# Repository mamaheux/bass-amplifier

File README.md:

# Bass-Amplifier
Bass-Amplifier is a project to create our own bass guitar amplifier. The amplifier features are:
 - Digital sound processing
 - Footswitch
 - Tuner output
 - XLR and jack direct output
 - Effect send and return
 - Contour and presence filters
 - 4-band EQ
 - Compressor effect
 - Overdrive effect
 - Octaver effect
 - Delay effect
 - Reverb effect

## Folder Descriptions
### cases
This folder contains the CAD files to create the cases.

### code
This folder contains the MCU source code for the footswitch, the bass amplifier signal processor and the bass amplifier controller.

### electronics
This folder contains the schematics and PCB layouts of the bass amplifier.

### tools/signal_processing
This folder contains a Python tool to test the audio effects.

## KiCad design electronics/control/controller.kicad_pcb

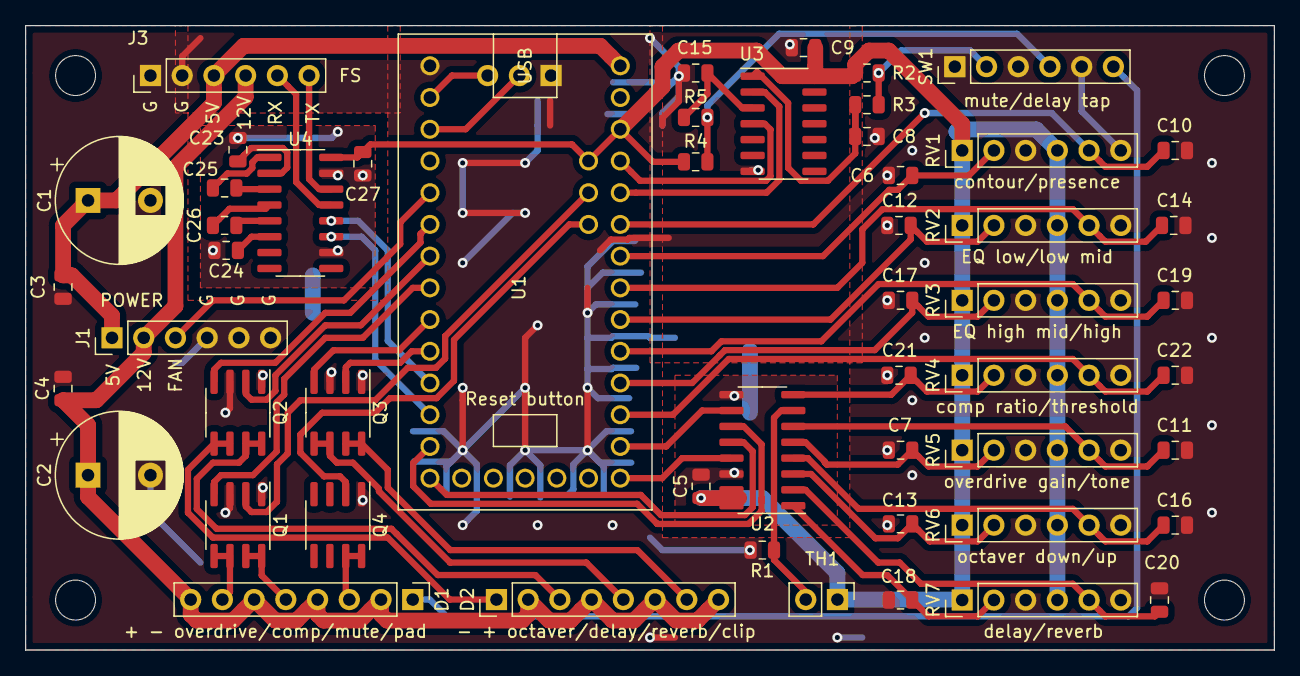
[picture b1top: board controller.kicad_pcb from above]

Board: 2 copper layers, 100.0 x 50.0 mm, 54 parts (1 on the bottom side), 57 nets.

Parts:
C1, C2: 1000µF/25V; CP_Radial_D10.0mm_P5.00mm
C3, C4: 2.2µF/25V/UL low ESR; C_0805_2012Metric
C5, C9: 1µF/10V/UL ESR; C_0805_2012Metric
C6, C7, C10, C11, C12, C13, C14, C16, C17, C18, C19, C20, C21, C22: 1µF/16V; C_0805_2012Metric
C8, C15: 0.1µF/25V; C_0805_2012Metric
C23, C24, C25, C26, C27: 0.1µF; C_0805_2012Metric
D1, D2: LED; PinHeader_1x08_P2.54mm_Vertical
J1: Conn_01x06_Male; PinHeader_1x06_P2.54mm_Vertical
J2: Conn_01x03_Male; PinHeader_1x03_P2.54mm_Vertical
J3: footswitch; PinHeader_1x06_P2.54mm_Vertical
Q1, Q2, Q3, Q4: TD9944; SOIC-8_3.9x4.9mm_P1.27mm
R1, R2, R3, R4, R5: 10k; R_0805_2012Metric
RV1, RV2, RV3, RV4, RV5, RV6, RV7: 10k; PinHeader_1x06_P2.54mm_Vertical
SW1: SW_SPST_X3; PinHeader_1x06_P2.54mm_Vertical
TH1: 10k; PinHeader_1x02_P2.54mm_Vertical
U1: Teensy_LC
U2: MCP3208; SOIC-16_3.9x9.9mm_P1.27mm
U3: 74HC14; SOIC-14_3.9x8.7mm_P1.27mm
U4: MAX3232; SOIC-16_3.9x9.9mm_P1.27mm

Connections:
/MCU/3V3: C5.1, C9.1, C27.1, R2.1, R4.1, RV1.1, RV1.4, RV2.1, RV2.4, RV3.1, RV3.4, RV4.1, RV4.4, RV5.1, RV5.4, RV6.1, RV6.4, RV7.1, RV7.4, TH1.1, U1.3V3_1, U1.AREF, U2.15, U2.16, U3.14, U4.16
/MCU/ADC_CS: U1.14, U2.10
/MCU/ADC_MISO: U1.12, U2.12
/MCU/ADC_MOSI: U1.11, U2.11
/MCU/ADC_SCK: U1.13, U2.13
/MCU/DSP_RX: J2.2, U1.1
/MCU/DSP_TX: J2.3, U1.0
/MCU/FS_RS232_RX: J3.5, U4.13
/MCU/FS_RS232_TX: J3.6, U4.14
/MCU/FS_RX: U1.9, U4.12
/MCU/FS_TX: U1.10, U4.11
/MCU/MCU_LED/clipping_LED: Q3.2, U1.8
/MCU/MCU_LED/delay_LED: Q2.2, U1.5
/MCU/MCU_LED/octaver_LED: Q2.4, U1.4
/MCU/MCU_LED/overdrive_LED: Q1.4, U1.6
/MCU/MCU_LED/reverb_LED: Q3.4, U1.7
/MCU/MCU_control_elements/EQ_high_mid_pot: C17.1, RV3.2, U1.16
/MCU/MCU_control_elements/EQ_high_pot: C19.1, RV3.5, U1.17
/MCU/MCU_control_elements/EQ_low_mid_pot: C14.1, RV2.5, U1.19
/MCU/MCU_control_elements/EQ_low_pot: C12.1, RV2.2, U1.18
/MCU/MCU_control_elements/comp_ratio_pot: C21.1, RV4.2, U2.8
/MCU/MCU_control_elements/comp_threshold_pot: C22.1, RV4.5, U1.15
/MCU/MCU_control_elements/contour_pot: C6.1, RV1.2, U1.20
/MCU/MCU_control_elements/delay_tap_button: U1.23, U3.4
/MCU/MCU_control_elements/delay_vol_pot: C18.1, RV7.2, U2.1
/MCU/MCU_control_elements/mute_sw: U1.22, U3.2
/MCU/MCU_control_elements/octaver_down_pot: C13.1, RV6.2, U2.3
/MCU/MCU_control_elements/octaver_up_pot: C16.1, RV6.5, U2.4
/MCU/MCU_control_elements/overdrive_gain_pot: C7.1, RV5.2, U2.5
/MCU/MCU_control_elements/overdrive_tone_pot: C11.1, RV5.5, U2.6
/MCU/MCU_control_elements/presence_pot: C10.1, RV1.5, U1.21
/MCU/MCU_control_elements/reverb_vol_pot: C20.1, RV7.5, U2.2
/MCU/V_temp: R1.1, TH1.2, U2.7
/MCU/comp_LED: Q1.2, U1.24
/MCU/fan_pwm: J1.3, U1.3
/MCU/mute_LED: Q4.2, U1.25
D+5V: C1.1, C3.1, J1.1, J3.3, U1.VIN
D+12V: C2.1, C4.1, D1.2, D1.4, D1.6, D1.8, D2.2, D2.4, D2.6, D2.8, J1.2, J3.4
GNDD: C1.2, C2.2, C3.2, C4.2, C5.2, C6.2, C7.2, C8.2, C9.2, C10.2, C11.2, C12.2, C13.2, C14.2, C15.2, C16.2, C17.2, C18.2, C19.2, C20.2, C21.2, C22.2, C23.2, C24.2, C27.2, J1.4, J1.5, J1.6, J2.1, J3.1, J3.2, Q1.1, Q1.3, Q2.1, Q2.3, Q3.1, Q3.3, Q4.1, R1.2, RV1.3, RV1.6, RV2.3, RV2.6, RV3.3, RV3.6, RV4.3, RV4.6, RV5.3, RV5.6, RV6.3, RV6.6, RV7.3, RV7.6, SW1.1, SW1.3, SW1.5, U1.GND_1, U2.9, U2.14, U3.7, U4.10, U4.15
unnamed: C8.1, R3.1, U3.1
unnamed: C15.1, R5.1, U3.3
unnamed: C23.1, U4.2
unnamed: C24.1, U4.6
unnamed: C25.1, U4.3
unnamed: C25.2, U4.1
unnamed: C26.1, U4.5
unnamed: C26.2, U4.4
unnamed: D1.1, SW1.6
unnamed: D1.3, Q4.7, Q4.8
unnamed: D1.5, Q1.7, Q1.8
unnamed: D1.7, Q1.5, Q1.6
unnamed: D2.1, Q2.5, Q2.6
unnamed: D2.3, Q2.7, Q2.8
unnamed: D2.5, Q3.5, Q3.6
unnamed: D2.7, Q3.7, Q3.8
unnamed: R2.2, R3.2, SW1.2
unnamed: R4.2, R5.2, SW1.4

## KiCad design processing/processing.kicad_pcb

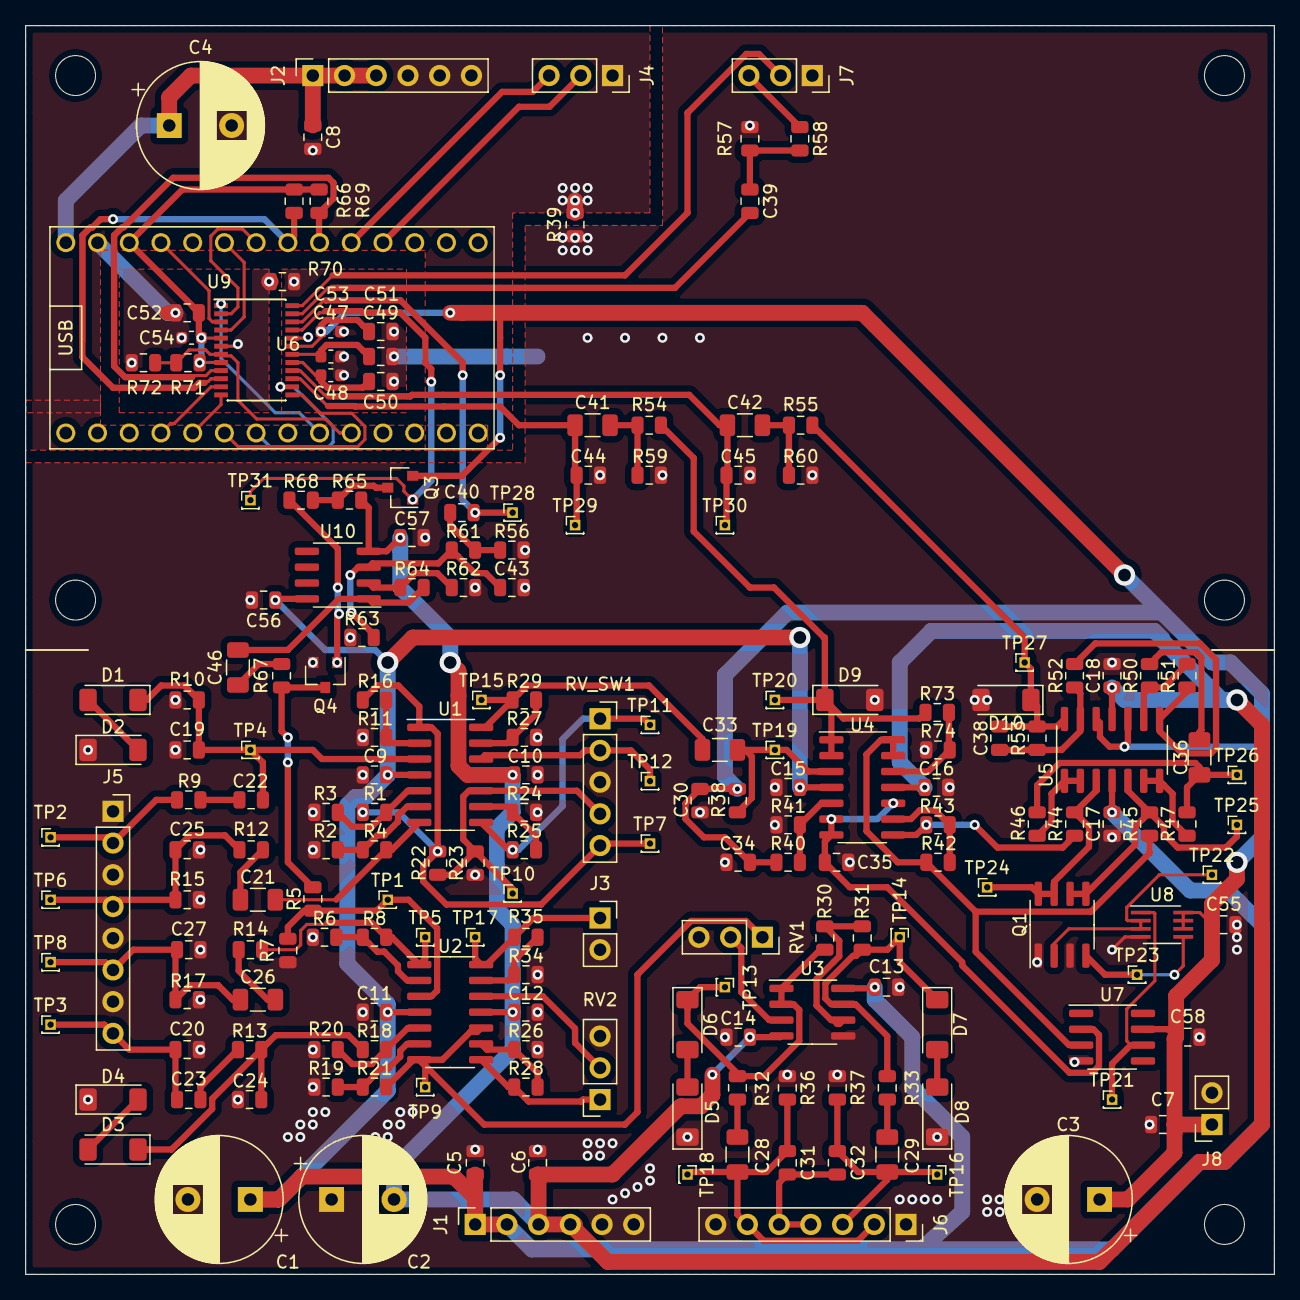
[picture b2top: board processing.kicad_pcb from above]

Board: 2 copper layers, 100.0 x 100.0 mm, 194 parts (0 on the bottom side), 106 nets.

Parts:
C1, C2, C3, C4: 1000µF/25V; CP_Radial_D10.0mm_P5.00mm
C5, C6, C7, C8, C9, C10, C11, C12, C13, C14, C15, C16, C17, C18, C30, C34, C35, C55, C56, C57, C58: 2.2µF/25V/UL ESR; C_0805_2012Metric
C19: 100pF/100V; C_0805_2012Metric
C20, C24: 220pF/100V; C_0805_2012Metric
C21, C26, C28, C29, C33, C36, C41, C42, C46: 10µF/50V; C_1206_3216Metric
C22: 0.1µF/100V; C_0805_2012Metric
C23: 0.22µF/100V; C_0805_2012Metric
C25: 1nF/100V; C_0805_2012Metric
C27, C31, C32: 4.7nF/100V; C_0805_2012Metric
C38: 0.047µF/100V; C_0805_2012Metric
C39, C40: 3.3µF/25V; C_0805_2012Metric
C43: 3600pF/50V; C_0805_2012Metric
C44, C45: 220pF/50V; C_0805_2012Metric
C47, C48, C53, C54: 0.1µF/25V; C_0603_1608Metric
C49: 47µF/10V; C_0805_2012Metric
C50: 10µF/10V; C_0805_2012Metric
C51, C52: 1µF/6.3V; C_0805_2012Metric
D1, D2, D3, D4, D5, D6, D7, D8: 12V; D_1806_4516Metric
D9, D10: 6.2V; D_1806_4516Metric
J1, J2: Conn_01x06_Male; PinSocket_1x06_P2.54mm_Vertical
J3: power_amp; PinSocket_1x02_P2.54mm_Vertical
J4: control board; PinSocket_1x03_P2.54mm_Vertical
J5: AudioJack2_X4; PinSocket_1x08_P2.54mm_Vertical
J6: AudioJack2_XLR_SW; PinSocket_1x07_P2.54mm_Vertical
J7: Conn_01x03_Male; PinSocket_1x03_P2.54mm_Vertical
J8: Conn_01x02_Male; PinSocket_1x02_P2.54mm_Vertical
Q1: TD9944; SOIC-8_3.9x4.9mm_P1.27mm
Q3: MMUN2111LT1; SOT-23
Q4: MMBT2222A; SOT-23
R1, R4, R5, R8, R16, R18, R21, R39, R70: 0; R_0805_2012Metric
R2, R6, R11, R19: inf; R_0805_2012Metric
R3, R12, R15, R30, R31, R38, R40, R41, R42, R43, R53, R56, R57, R63, R65, R73, R74: 10k; R_0805_2012Metric
R7: 47.5k; R_0805_2012Metric
R9: 12.1K; R_0805_2012Metric
R10: 1M; R_0805_2012Metric
R13: 12.1k; R_0805_2012Metric
R14: 221; R_0805_2012Metric
R17: 2.21k; R_0805_2012Metric
R20: 56.2k; R_0805_2012Metric
R22: 23.7k; R_0805_2012Metric
R23, R24, R27, R28, R35, R46, R47, R50: 5.11k; R_0805_2012Metric
R25, R29, R44, R45, R51: 20k; R_0805_2012Metric
R26, R34: 10.2k; R_0805_2012Metric
R32, R33: 1k; R_0805_2012Metric
R36, R37: 100k; R_0805_2012Metric
R52: 4.75k; R_0805_2012Metric
R54, R55, R59, R60, R66, R68, R69: 2k; R_0805_2012Metric
R58, R61: 470; R_0805_2012Metric
R62: 3.09k; R_0805_2012Metric
R64: 15.4k; R_0805_2012Metric
R67: 560; R_0805_2012Metric
R71, R72: inf or 47k; R_0805_2012Metric
RV1, RV2: R_POT; PinSocket_1x03_P2.54mm_Vertical
RV_SW1: 10k; PinSocket_1x05_P2.54mm_Vertical
TP1, TP2, TP3, TP4, TP5, TP6, TP7, TP8, TP9, TP10, TP11, TP12, TP13, TP14, TP15, TP16, TP17, TP18, TP19, TP20, TP21, TP22, TP23, TP24, TP25, TP26, TP27, TP28, TP29, TP30, TP31: TP; PinHeader_1x01_P1.00mm_Vertical
U1, U2, U4, U5: TL074; SOIC-14_3.9x8.7mm_P1.27mm
U3, U10: TL072; SOIC-8_3.9x4.9mm_P1.27mm
U6: Teensy_4.0
U7: MCP6541; SOIC-8_3.9x4.9mm_P1.27mm
U8: SN74AUC1G74; SSOP-8_2.95x2.8mm_P0.65mm
U9: CS4270; TSSOP-24_4.4x7.8mm_P0.65mm

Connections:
/LRCLK: U6.20, U9.2
/MCLK: U6.23, U9.3
/MCU_3.3V: C52.1, C54.1, R66.1, R69.1, R71.2, U6.3V3_1, U9.5, U9.8
/SCL: R66.2, U6.19, U9.10
/SCLK: U6.21, U9.4
/SDA: R69.2, U6.18, U9.9
/SDIN: U6.7, U9.1
/SDOUT: R71.1, R72.2, U6.8, U9.7
/analog/octaver_down/REF+1.65V: C35.1, U4.6, U4.7, U4.10, U7.2
/analog/octaver_down/half_signal_in: R42.2, R45.2, U4.13, U4.14, U7.3
/analog/power_amp_signal: J3.1, R35.1, TP17.1, U2.14
/codec/AD0: U6.2, U9.11
/codec/AD1: U6.3, U9.12
/codec/AD2: U6.4, U9.13
/codec/ADC_input_A: D9.1, R54.2, R73.2, TP20.1, U4.1, U4.2
/codec/ADC_input_B: C38.1, D10.1, R53.1, R55.2, TP27.1, U5.14
/codec/DAC_output: Q4.3, R5.2, R67.1
/codec/INA: C41.1, C44.2, TP29.1, U9.15
/codec/INB: C42.1, C45.2, TP30.1, U9.16
/codec/OUTA: C40.2, TP28.1, U9.22
/codec/OUTB: C39.2, U9.23
/codec/~MUTEA: Q3.1, TP31.1, U9.21
/codec/~MUTEB: J7.2, U9.24
/codec/~RST: U6.5, U9.14
A+3.3V: C3.1, C7.1, C30.1, C34.1, C51.1, C53.1, C55.1, C58.1, J8.1, Q3.2, R38.1, R40.2, U5.10, U5.12, U7.7, U8.6, U8.7, U8.8, U9.19
A+15V: C1.1, C5.1, C9.1, C11.1, C13.1, C15.1, C17.1, C56.1, J1.1, J1.2, U1.4, U2.4, U3.8, U4.4, U5.4, U10.8
A-15V: C2.2, C6.2, C10.1, C12.1, C14.1, C16.1, C18.1, C57.1, J1.3, J1.4, R65.1, U1.11, U2.11, U3.4, U4.11, U5.11, U10.4
D+5V: C4.1, C8.1, J2.1, J2.2, J2.3, U6.VIN
GNDA: C1.2, C2.1, C3.2, C5.2, C6.1, C7.2, C9.2, C10.2, C11.2, C12.2, C13.2, C14.2, C15.2, C16.2, C17.2, C18.2, C19.1, C20.2, C24.2, C25.2, C27.2, C30.2, C34.2, C35.2, C43.1, C44.1, C45.1, C47.2, C48.1, C49.2, C50.1, C51.2, C53.2, C55.2, C56.2, C57.2, C58.2, D2.1, D4.1, D5.1, D8.1, D9.2, D10.2, J1.5, J1.6, J3.2, J5.1, J5.3, J5.5, J5.7, J6.1, J6.7, J7.1, J8.2, Q1.1, Q1.3, Q4.2, R2.2, R3.1, R6.2, R7.1, R10.1, R11.2, R15.2, R17.1, R19.2, R20.1, R23.1, R24.2, R26.2, R27.2, R34.2, R36.1, R37.1, R39.1, R41.1, R56.1, R57.1, R59.1, R60.1, R62.2, R63.1, R70.1, R74.1, RV1.3, RV2.3, RV_SW1.3, U3.5, U7.4, U8.4, U9.20
GNDD: C4.2, C8.2, C52.2, C54.2, J2.4, J2.5, J2.6, J4.1, R39.2, R70.2, R72.1, U6.GND_2, U9.6
unnamed: C19.2, C22.1, D1.1, R10.2, TP4.1, U1.3
unnamed: C20.1, C23.1, J5.8, TP3.1
unnamed: C21.1, R12.2
unnamed: C21.2, R4.1, U1.7
unnamed: C22.2, R9.1
unnamed: C23.2, R13.2
unnamed: C24.1, D3.1, R13.1, R18.2
unnamed: C25.1, J5.4, R12.1, R15.1, TP6.1
unnamed: C26.1, C27.1, J5.6, R17.2, TP8.1
unnamed: C26.2, R14.1
unnamed: C28.1, C31.1, J6.2, J6.6, R36.2, TP18.1
unnamed: C28.2, R32.1
unnamed: C29.1, C32.1, J6.3, R37.2, TP16.1
unnamed: C29.2, R33.1
unnamed: C31.2, C32.2, J6.4, J6.5
unnamed: C33.1, R38.2, TP19.1, U4.3
unnamed: C33.2, R29.1, TP15.1, U1.14
unnamed: C36.1, R50.2
unnamed: C36.2, R46.1, R47.2, TP26.1
unnamed: C38.2, R52.1, R53.2, U5.13
unnamed: C39.1, R57.2, R58.2
unnamed: C40.1, R56.2, R61.2
unnamed: C41.2, R54.1, R59.2
unnamed: C42.2, R55.1, R60.2
unnamed: C43.2, R61.1, R63.2, U10.3
unnamed: C46.1, R67.2
unnamed: C46.2, R64.1, U10.1
unnamed: C47.1, C49.1, U9.18
unnamed: C48.2, C50.2, U9.17
unnamed: D1.2, D2.2
unnamed: D3.2, D4.2
unnamed: D5.2, D6.2
unnamed: D6.1, R30.1, R32.2, TP13.1, U3.1, U3.2
unnamed: D7.1, R31.1, R33.2, TP14.1, U3.7
unnamed: D7.2, D8.2
unnamed: J4.2, U6.16
unnamed: J4.3, U6.17
unnamed: J5.2, R9.2, TP2.1
unnamed: J7.3, R58.1
unnamed: Q1.2, TP22.1, U8.2, U8.3
unnamed: Q1.4, TP23.1, U8.5
unnamed: Q1.5, Q1.6, R45.1, TP25.1, U5.5
unnamed: Q1.7, Q1.8, R44.1, TP24.1, U5.3
unnamed: Q3.3, R65.2, R68.1
unnamed: Q4.1, R68.2
unnamed: R1.1, R3.2, U1.5
unnamed: R1.2, R16.1, R22.2, RV_SW1.5, TP7.1, U1.1
unnamed: R2.1, R4.2, U1.6
unnamed: R5.1, R7.2, TP1.1, U2.3
unnamed: R6.1, R8.2, U2.2
unnamed: R11.1, R16.2, U1.2
unnamed: R8.1, R14.2, TP5.1, U2.1
unnamed: R18.1, R20.2, U2.5
unnamed: R19.1, R21.2, U2.6
unnamed: R21.1, RV1.1, TP9.1, U2.7, U2.10
unnamed: R22.1, R23.2, RV_SW1.4, TP10.1, U1.10
unnamed: R24.1, R25.2, U1.9
unnamed: R25.1, RV_SW1.1, TP11.1, U1.8
unnamed: R26.1, R28.2, U2.9
unnamed: R27.1, R29.2, U1.13
unnamed: R28.1, RV2.1, U2.8
unnamed: R30.2, R31.2, U3.6
unnamed: R34.1, R35.2, U2.13
unnamed: R40.1, R41.2, U4.5
unnamed: R42.1, R43.2, U4.9
unnamed: R43.1, R44.2, U4.8
unnamed: R46.2, U5.1, U5.2
unnamed: R47.1, U5.6, U5.7
unnamed: R50.1, R51.2, U5.9
unnamed: R51.1, R52.2, U5.8
unnamed: R62.1, R64.2, U10.2
unnamed: R73.1, R74.2, U4.12
unnamed: RV1.2, U3.3
unnamed: RV2.2, U2.12
unnamed: RV_SW1.2, TP12.1, U1.12
unnamed: TP21.1, U7.6, U8.1

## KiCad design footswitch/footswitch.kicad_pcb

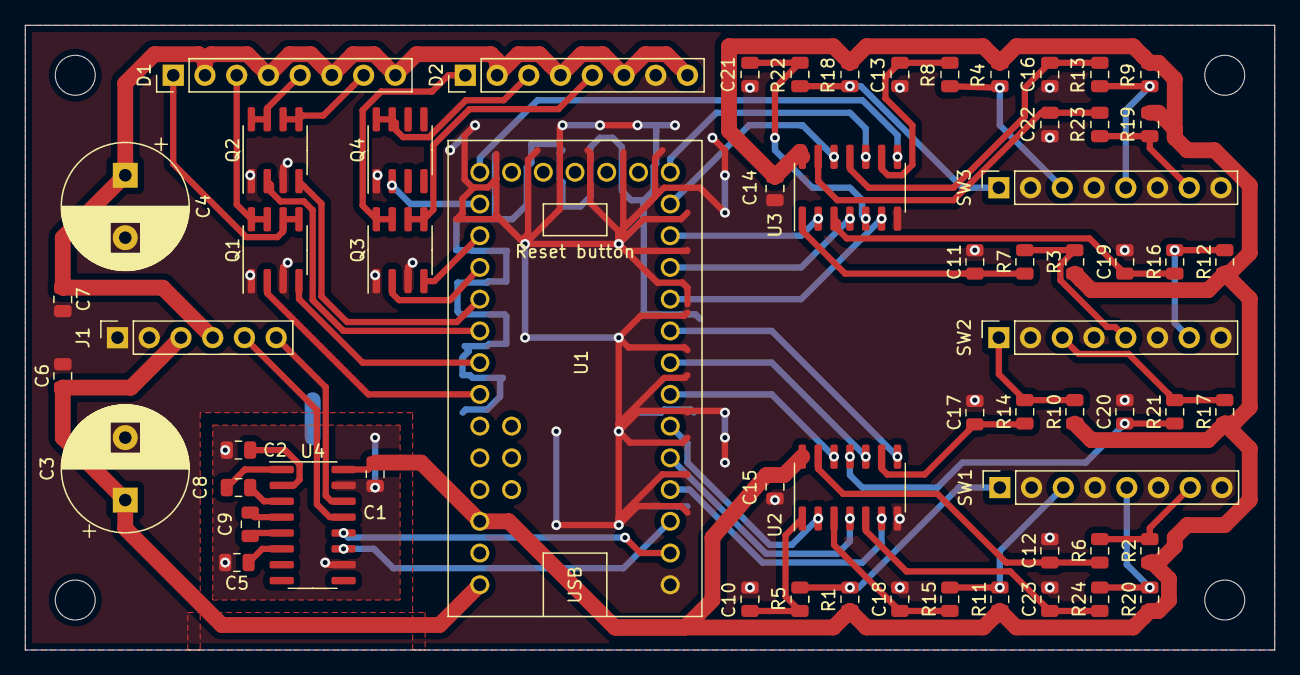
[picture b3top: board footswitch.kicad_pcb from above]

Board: 2 copper layers, 100.0 x 50.0 mm, 61 parts (0 on the bottom side), 64 nets.

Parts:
C1, C2, C5, C8, C9, C10, C11, C12, C13, C16, C17, C18, C19, C20, C21, C22, C23: 0.1µF/25V; C_0805_2012Metric
C3, C4: 1000µF/25V; CP_Radial_D10.0mm_P5.00mm
C6, C7: 2.2µF/25V/UL low ESR; C_0805_2012Metric
C14, C15: 1µF/10V/UL ESR; C_0805_2012Metric
D1, D2: LED; PinHeader_1x08_P2.54mm_Vertical
J1: control; PinSocket_1x06_P2.54mm_Vertical
Q1, Q2, Q3, Q4: TD9944; SOIC-8_3.9x4.9mm_P1.27mm
R1, R2, R3, R4, R5, R6, R7, R8, R9, R10, R11, R12, R13, R14, R15, R16, R17, R18, R19, R20, R21, R22, R23, R24: 10k; R_0805_2012Metric
SW1, SW2, SW3: SPST; PinSocket_1x08_P2.54mm_Vertical
U1: Teensy_LC
U2, U3: 74HC14; SOIC-14_3.9x8.7mm_P1.27mm
U4: MAX3232; SOIC-16_3.9x9.9mm_P1.27mm

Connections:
/3V3: C1.2, C14.1, C15.1, R1.1, R2.1, R3.1, R4.1, R9.1, R10.1, R11.1, R12.1, R17.1, R18.1, R19.1, R20.1, U1.3V3_1, U2.14, U3.14, U4.16
/MCU_LED/clipping_LED: Q1.4, U1.19
/MCU_LED/comp_LED: Q2.2, U1.18
/MCU_LED/delay_LED: Q4.2, U1.14
/MCU_LED/mute_LED: Q1.2, U1.20
/MCU_LED/octaver_LED: Q3.2, U1.16
/MCU_LED/overdrive_LED: Q2.4, U1.17
/MCU_LED/reverb_LED: Q3.4, U1.15
/MCU_switchs/comp_sw: U1.3, U2.4
/MCU_switchs/delay_sw: U1.7, U2.8
/MCU_switchs/delay_tap_button: U1.6, U2.10
/MCU_switchs/mute_sw: U1.4, U2.2
/MCU_switchs/octaver_sw: U1.5, U2.12
/MCU_switchs/opt_1_sw: U1.9, U3.4
/MCU_switchs/opt_2_sw: U1.8, U3.6
/MCU_switchs/opt_3_sw: U1.13, U3.8
/MCU_switchs/opt_4_sw: U1.12, U3.10
/MCU_switchs/opt_5_sw: U1.11, U3.12
/MCU_switchs/overdrive_sw: U1.2, U2.6
/MCU_switchs/reverb_sw: U1.10, U3.2
/control_RX: U1.0, U4.12
/control_TX: U1.1, U4.11
D+5V: C3.1, C6.1, J1.3, U1.VIN
D+12V: C4.1, C7.1, D1.2, D1.4, D1.6, D1.8, D2.2, D2.4, D2.6, D2.8, J1.4
GNDD: C1.1, C2.2, C3.2, C4.2, C5.2, C6.2, C7.2, C10.2, C11.2, C12.2, C13.2, C14.2, C15.2, C16.2, C17.2, C18.2, C19.2, C20.2, C21.2, C22.2, C23.2, D2.7, J1.1, J1.2, Q1.1, Q1.3, Q2.1, Q2.3, Q3.1, Q3.3, Q4.1, SW1.2, SW1.4, SW1.6, SW1.8, SW2.2, SW2.4, SW2.6, SW2.8, SW3.2, SW3.4, SW3.6, SW3.8, U1.GND_1, U2.7, U3.7, U4.10, U4.15
unnamed: C2.1, U4.2
unnamed: C5.1, U4.6
unnamed: C8.1, U4.1
unnamed: C8.2, U4.3
unnamed: C9.1, U4.4
unnamed: C9.2, U4.5
unnamed: C10.1, R5.1, U2.1
unnamed: C11.1, R7.1, U3.1
unnamed: C12.1, R6.1, U2.13
unnamed: C13.1, R8.1, U3.9
unnamed: C16.1, R13.1, U3.11
unnamed: C17.1, R14.1, U2.9
unnamed: C18.1, R15.1, U2.3
unnamed: C19.1, R16.1, U3.3
unnamed: C20.1, R21.1, U2.11
unnamed: C21.1, R22.1, U3.5
unnamed: C22.1, R23.1, U3.13
unnamed: C23.1, R24.1, U2.5
unnamed: D1.1, Q1.5, Q1.6
unnamed: D1.3, Q1.7, Q1.8
unnamed: D1.5, Q2.7, Q2.8
unnamed: D1.7, Q2.5, Q2.6
unnamed: D2.1, Q3.7, Q3.8
unnamed: D2.3, Q4.7, Q4.8
unnamed: D2.5, Q3.5, Q3.6
unnamed: J1.5, U4.13
unnamed: J1.6, U4.14
unnamed: R1.2, R5.2, SW1.1
unnamed: R2.2, R6.2, SW1.7
unnamed: R3.2, R7.2, SW2.5
unnamed: R4.2, R8.2, SW3.3
unnamed: R10.2, R14.2, SW2.1
unnamed: R11.2, R15.2, SW1.3
unnamed: R12.2, R16.2, SW2.7
unnamed: R9.2, R13.2, SW3.5
unnamed: R17.2, R21.2, SW2.3
unnamed: R18.2, R22.2, SW3.1
unnamed: R19.2, R23.2, SW3.7
unnamed: R20.2, R24.2, SW1.5

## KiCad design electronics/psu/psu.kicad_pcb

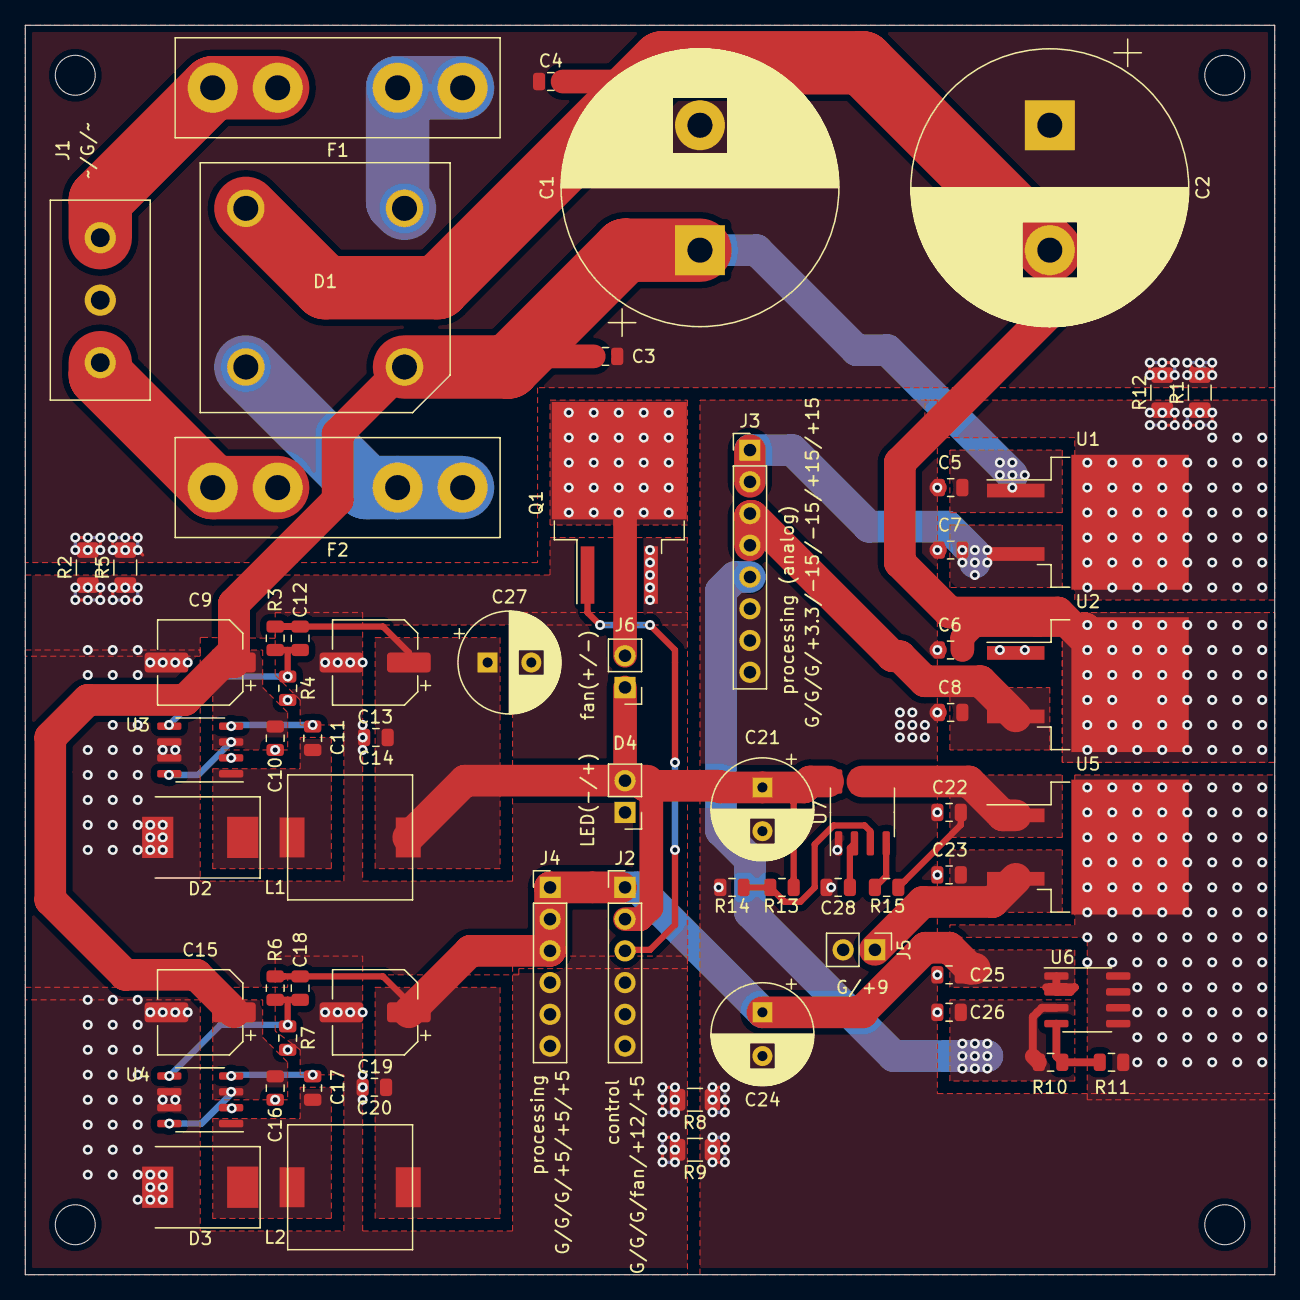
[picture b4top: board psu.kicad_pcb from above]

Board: 2 copper layers, 100.0 x 100.0 mm, 65 parts (0 on the bottom side), 28 nets.

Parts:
C1, C2: 10000µF/35V; CP_Radial_D22.0mm_P10.00mm_SnapIn
C3, C4, C5, C6, C10, C16, C25: 1µF/35V; C_0805_2012Metric
C7, C8, C14, C20, C22, C23: 2.2µF/25V/UL ESR; C_0805_2012Metric
C9, C15: 33µF/35V/260mOhm; CP_Elec_6.3x7.7
C11, C17: 0.33µF; C_0805_2012Metric
C12, C18: 0.1µF; C_0805_2012Metric
C13, C19: 330µF/6.3V/160mOhm; CP_Elec_6.3x7.7
C21, C24, C27: 470µF/16V; CP_Radial_D8.0mm_P3.50mm
C26: 47µF/6.3V; C_0805_2012Metric
C28: C; C_0805_2012Metric
D1: BR81
D2, D3: SS34/40V/4A; D_SMC
D4: LED; PinHeader_1x02_P2.54mm_Vertical
F1, F2: 1.5A; M205_FUSE
J1: Conn_01x03_Female; transformer_connector
J2: control board; PinHeader_1x06_P2.54mm_Vertical
J3: processing; PinHeader_1x08_P2.54mm_Vertical
J4: processing; PinHeader_1x06_P2.54mm_Vertical
J5: pedals; PinHeader_1x02_P2.54mm_Vertical
J6: FAN; PinHeader_1x02_P2.54mm_Vertical
L1, L2: 68µH/Sumida CDRH104R-680MC; CDRH104RNP-680NC
Q1: PHB21N06LT; TO-263-2
R1, R2, R5, R8, R9, R12: 0; R_1206_3216Metric
R3, R6: 3.01k; R_0805_2012Metric
R4: 348; R_0805_2012Metric
R7: 976; R_0805_2012Metric
R10: 16.5k; R_0805_2012Metric
R11: 10k; R_0805_2012Metric
R13, R14: inf; R_0805_2012Metric
R15: 309; R_0805_2012Metric
U1: MC7815; TO-263-2
U2: MC7915; TO-263-2
U3, U4: MIC4684; SOIC-8_3.9x4.9mm_P1.27mm
U5: MC7809; TO-263-2
U6: MIC37152; SOIC-8_3.9x4.9mm_P1.27mm
U7: NIS5112; SOIC-8_3.9x4.9mm_P1.27mm

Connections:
/+20V: C1.1, C3.1, C5.1, C9.1, C10.1, C15.1, C16.1, D1.1, U1.1, U3.3, U3.8, U4.3, U4.8
/-20V: C2.2, C4.2, C6.2, D1.2, U2.2
/A+3.3V: C26.1, J3.5, R10.1, U6.3
/A+9V: C23.1, J5.1, U5.3
/A+15V: C7.1, J3.1, J3.2, U1.3
/A-15V: C8.2, J3.3, J3.4, U2.3
/D+5V: C18.1, C19.1, C20.1, C24.1, C25.1, J2.1, J4.1, J4.2, J4.3, L2.2, R6.1, U6.1, U6.2
/D+12V: C12.1, C13.1, C14.1, C21.1, C27.1, D4.2, J2.2, J6.1, L1.2, R3.1, R13.2, U7.8
/fan/fan_pwm: J2.3, Q1.1
GND: C1.2, C2.1, C3.2, C4.1, J1.2, R1.2, R2.2, R5.2, R12.2
GNDA: C5.2, C6.1, C7.2, C8.1, C21.2, C22.2, C23.2, C24.2, C25.2, C26.2, C28.2, J3.6, J3.7, J3.8, J5.2, R1.1, R8.1, R9.1, R11.2, R12.1, R14.2, U1.2, U2.1, U5.2, U6.5, U6.6, U6.7, U6.8, U7.1
GNDD: C9.2, C10.2, C13.2, C14.2, C15.2, C16.2, C19.2, C20.2, C27.2, D2.2, D3.2, D4.1, J2.4, J2.5, J2.6, J4.4, J4.5, J4.6, Q1.3, R2.1, R4.2, R5.1, R7.2, R8.2, R9.2, U3.2, U3.6, U3.7, U4.2, U4.6, U4.7
unnamed: C11.1, U3.4
unnamed: C11.2, D2.1, L1.1, U3.1
unnamed: C12.2, R3.2, R4.1, U3.5
unnamed: C17.1, U4.4
unnamed: C17.2, D3.1, L2.1, U4.1
unnamed: C18.2, R6.2, R7.1, U4.5
unnamed: C22.1, R15.2, U5.1, U7.5, U7.6, U7.7
unnamed: C28.1, U7.2
unnamed: D1.3, F2.1
unnamed: D1.4, F1.1
unnamed: F1.2, J1.3
unnamed: F2.2, J1.1
unnamed: J6.2, Q1.2
unnamed: R10.2, R11.1, U6.4
unnamed: R13.1, R14.1, U7.3
unnamed: R15.1, U7.4

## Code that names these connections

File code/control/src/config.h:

#ifndef CONFIG_H
#define CONFIG_H

#include <Arduino.h>
#include <SPI.h>

// Effects
constexpr float SAMPLING_FREQUENCY = 48000;
constexpr uint32_t MAX_DELAY = 96000;

// IO
#define DEBUG_SERIAL Serial
#define FOOTSWITCH_SERIAL Serial2
#define DSP_SERIAL Serial1

constexpr uint8_t ADC_RESOLUTION = 12;
constexpr uint16_t ADC_MAX_VALUE = 4095;

#define EXTERNAL_ADC_SPI SPI
constexpr uint32_t EXTERNAL_ADC_SPI_CLK = 1600000;
constexpr uint8_t EXTERNAL_ADC_CS_PIN = 14;

enum class AdcSource
{
    INTERNAL_ADC,
    EXTERNAL_ADC
};

struct AdcChannel
{
    AdcSource source;
    uint8_t channel;
};

constexpr uint16_t POT_DEAD_ZONE = 64;

constexpr AdcChannel CONTOUR_GAIN_POT = {AdcSource::INTERNAL_ADC, 20};
constexpr AdcChannel PRESENCE_GAIN_POT = {AdcSource::INTERNAL_ADC, 21};
constexpr AdcChannel EQ_LOW_GAIN_POT = {AdcSource::INTERNAL_ADC, 18};
constexpr AdcChannel EQ_LOW_MID_GAIN_POT = {AdcSource::INTERNAL_ADC, 19};
constexpr AdcChannel EQ_HIGH_MID_GAIN_POT = {AdcSource::INTERNAL_ADC, 16};
constexpr AdcChannel EQ_HIGH_GAIN_POT = {AdcSource::INTERNAL_ADC, 17};
constexpr AdcChannel COMPRESSOR_THRESHOLD_POT = {AdcSource::INTERNAL_ADC, 15};
constexpr AdcChannel COMPRESSOR_RATIO_POT = {AdcSource::EXTERNAL_ADC, 7};
constexpr AdcChannel OCTAVER_DOWM_VOLUME_POT = {AdcSource::EXTERNAL_ADC, 2};
constexpr AdcChannel OCTAVER_UP_VOLUME_POT = {AdcSource::EXTERNAL_ADC, 3};
constexpr AdcChannel DELAY_VOLUME_POT = {AdcSource::EXTERNAL_ADC, 0};
constexpr AdcChannel REVERB_VOLUME_POT = {AdcSource::EXTERNAL_ADC, 1};
constexpr AdcChannel OVERDRIVE_GAIN_POT = {AdcSource::EXTERNAL_ADC, 4};
constexpr AdcChannel OVERDRIVE_TONE_POT = {AdcSource::EXTERNAL_ADC, 5};

constexpr uint8_t DELAY_TAP_PIN = 23;
constexpr uint8_t MUTE_PIN = 22;


constexpr uint8_t COMPRESSOR_LED_PIN = 24;
constexpr uint8_t OCTAVER_LED_PIN = 4;
constexpr uint8_t DELAY_LED_PIN = 5;
constexpr uint8_t REVERB_LED_PIN = 7;
constexpr uint8_t OVERDRIVE_LED_PIN = 6;
constexpr uint8_t MUTE_LED_PIN = 25;
constexpr uint8_t CLIPPING_LED_PIN = 8;

// Other
constexpr uint32_t CLIPPING_LED_ON_DURATION_MS = 500;

#endif

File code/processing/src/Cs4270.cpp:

#include "Cs4270.h"

#include "InterruptLock.h"

static constexpr uint32_t I2S_TCSR_FRF = 0x00010000;
static constexpr uint32_t I2S_RCSR_FRF = 0x00010000;

static constexpr uint32_t TX_FIFO_WATERMARK = 28;
static constexpr uint32_t RX_FIFO_WATERMARK = 1;


static Cs4270Buffer<BLOCK_SIZE>* leftInputBuffer;
static Cs4270Buffer<BLOCK_SIZE>* rightInputBuffer;
static Cs4270Buffer<BLOCK_SIZE>* leftOutputBuffer;
static Cs4270Buffer<BLOCK_SIZE>* rightOutputBuffer;

static void cs4270Interrupt()
{
    constexpr int32_t SAMPLE_MASK = 0xFFFFFF00;

    if (I2S1_TCSR & I2S_TCSR_FRF)
    {
        // Write samples
        int32_t leftSample = 0;
        int32_t rightSample = 0;

        leftOutputBuffer->read(leftSample);
        rightOutputBuffer->read(rightSample);

        I2S1_TDR0 = leftSample & SAMPLE_MASK;
        I2S1_TDR0 = rightSample & SAMPLE_MASK;
    }

    if (I2S1_RCSR & I2S_RCSR_FRF)
    {
        // Read samples
        int32_t leftSample = I2S1_RDR0;
        int32_t rightSample = I2S1_RDR0;

        leftInputBuffer->write(leftSample & SAMPLE_MASK);
        rightInputBuffer->write(rightSample & SAMPLE_MASK);
    }
}


Cs4270::Cs4270()
{
    static_assert(CS4270_SDIN_PIN == 7, "Invalid SDIN pin");
    static_assert(CS4270_SDOUT_PIN == 8, "Invalid SDOUT pin");
    static_assert(CS4270_LRCLK_PIN == 20, "Invalid LRCLK pin");
    static_assert(CS4270_SCLK_PIN == 21, "Invalid SCLK pin");
    static_assert(CS4270_MCLK_PIN == 23, "Invalid MCLK pin");
}

void Cs4270::begin()
{
    CCM_CCGR5 |= CCM_CCGR5_SAI1(CCM_CCGR_ON);

    setupCs4270();
    setupI2s();
}

bool Cs4270::read(float* leftBlock, float* rightBlock)
{
    InterruptLock lock(IRQ_SAI1);
    if (m_leftInputBuffer.readAvailable() < BLOCK_SIZE || m_rightInputBuffer.readAvailable() < BLOCK_SIZE)
    {
        return false;
    }


    for (uint32_t i = 0; i < BLOCK_SIZE; i++)
    {
        int32_t leftSample;
        int32_t rightSample;

        m_leftInputBuffer.read(leftSample);
        m_rightInputBuffer.read(rightSample);

        leftBlock[i] = int32ToFloat(leftSample);
        rightBlock[i] = int32ToFloat(rightSample);
    }

    return true;
}

bool Cs4270::write(float* leftBlock, float* rightBlock)
{
    InterruptLock lock(IRQ_SAI1);
    if (m_leftOutputBuffer.writeAvailable() < BLOCK_SIZE || m_rightOutputBuffer.writeAvailable() < BLOCK_SIZE)
    {
        return false;
    }

    for (uint32_t i = 0; i < BLOCK_SIZE; i++)
    {
        m_leftOutputBuffer.write(floatToInt32(leftBlock[i]));
        m_rightOutputBuffer.write(floatToInt32(rightBlock[i]));
    }

    return true;
}

void Cs4270::setupCs4270()
{
    setupCs4270Pins();

    CS4270_I2C.begin();
    setupCs4270Parameters();
}

void Cs4270::setupCs4270Pins()
{
    pinMode(CS4270_AD0_PIN, OUTPUT);
    digitalWrite(CS4270_AD0_PIN, LOW);

    pinMode(CS4270_AD1_PIN, OUTPUT);
    digitalWrite(CS4270_AD1_PIN, LOW);

    pinMode(CS4270_AD2_PIN, OUTPUT);
    digitalWrite(CS4270_AD2_PIN, HIGH);

    pinMode(CS4270_RESET_PIN, OUTPUT);
    digitalWrite(CS4270_RESET_PIN, HIGH);
}

void Cs4270::setupCs4270Parameters()
{
    // Default values are good.
}

void Cs4270::setupI2s()
{
    // if TX or RX are enabled
    if ((I2S1_TCSR & I2S_TCSR_TE) || (I2S1_RCSR & I2S_RCSR_RE)) return;

    setupI2sClocks();

    //Setup I2S (TX is sync and RX is async because TX and RX must use RX_BCLK and RX_SYNC)
    setupI2sTx();
    setupI2sRx();

    setupInterrupt();

    enableI2s();
}

void Cs4270::setupI2sClocks()
{
    int n1;
    int n2;
    setupPLL4(n1, n2);
    // Setup SAI1_CLK
    CCM_CSCMR1 = (CCM_CSCMR1 & ~(CCM_CSCMR1_SAI1_CLK_SEL_MASK)) | CCM_CSCMR1_SAI1_CLK_SEL(2); // Set PLL4 clock source
    CCM_CS1CDR = (CCM_CS1CDR & ~(CCM_CS1CDR_SAI1_CLK_PRED_MASK | CCM_CS1CDR_SAI1_CLK_PODF_MASK))
           | CCM_CS1CDR_SAI1_CLK_PRED(n1 - 1) // Set clock pred to n1 (1 <= n1 <= 8)
           | CCM_CS1CDR_SAI1_CLK_PODF(n2 - 1); // Set clock prodf to n1 (1 <= n1 <= 2^6)

    // Setup MCLK1
    IOMUXC_GPR_GPR1 = (IOMUXC_GPR_GPR1 & ~(IOMUXC_GPR_GPR1_SAI1_MCLK1_SEL_MASK))
        | IOMUXC_GPR_GPR1_SAI1_MCLK_DIR // Set MCLK as an output
        | IOMUXC_GPR_GPR1_SAI1_MCLK1_SEL(0); // Set MCLK source to ccm.ssi1_clk_root

    // Setup clock pins
    CORE_PIN23_CONFIG = 3;  // Set pin23 as MCLK
    CORE_PIN21_CONFIG = 3;  // Set pin21 as RX_BCLK
    CORE_PIN20_CONFIG = 3;  // Set pin20 as RX_SYNC
}

void Cs4270::setupPLL4(int& n1, int& n2)
{
    int fs = SAMPLING_FREQUENCY;
    n1 = 4;
    n2 = 1 + (24000000 * 27) / (fs * 256 * n1);

    double C = ((double)fs * 256 * n1 * n2) / 24000000;
    int c0 = C;
    uint32_t c2 = 10000;
    int32_t c1 = C * c2 - (c0 * c2);

    // From :https://github.com/PaulStoffregen/Audio/blob/master/utility/imxrt_hw.cpp
    if (CCM_ANALOG_PLL_AUDIO & CCM_ANALOG_PLL_AUDIO_ENABLE) return;

    CCM_ANALOG_PLL_AUDIO = CCM_ANALOG_PLL_AUDIO_BYPASS | CCM_ANALOG_PLL_AUDIO_ENABLE
                 | CCM_ANALOG_PLL_AUDIO_POST_DIV_SELECT(2) // 2: 1/4; 1: 1/2; 0: 1/1
                 | CCM_ANALOG_PLL_AUDIO_DIV_SELECT(c0);

    CCM_ANALOG_PLL_AUDIO_NUM   = c1 & CCM_ANALOG_PLL_AUDIO_NUM_MASK;
    CCM_ANALOG_PLL_AUDIO_DENOM = c2 & CCM_ANALOG_PLL_AUDIO_DENOM_MASK;

    CCM_ANALOG_PLL_AUDIO &= ~CCM_ANALOG_PLL_AUDIO_POWERDOWN;//Switch on PLL
    while (!(CCM_ANALOG_PLL_AUDIO & CCM_ANALOG_PLL_AUDIO_LOCK)) {}; //Wait for pll-lock

    const int div_post_pll = 1; // other values: 2,4
    CCM_ANALOG_MISC2 &= ~(CCM_ANALOG_MISC2_DIV_MSB | CCM_ANALOG_MISC2_DIV_LSB);
    if(div_post_pll>1) CCM_ANALOG_MISC2 |= CCM_ANALOG_MISC2_DIV_LSB;
    if(div_post_pll>3) CCM_ANALOG_MISC2 |= CCM_ANALOG_MISC2_DIV_MSB;

    CCM_ANALOG_PLL_AUDIO &= ~CCM_ANALOG_PLL_AUDIO_BYPASS;//Disable Bypass
}

void Cs4270::setupI2sTx()
{
    I2S1_TMR = 0; // Set the transmit mask to 0
    I2S1_TCR1 = I2S_TCR1_RFW(TX_FIFO_WATERMARK); // Set the FIFO watermark
    I2S1_TCR2 = I2S_TCR2_SYNC(1) // Set TX mode to sync
        | I2S_TCR2_BCP // Set BCLK active low
        | I2S_TCR2_BCD // Set BCLK as an output
        | I2S_TCR2_DIV(1) // Set bit clock divide to 4
        | I2S_TCR2_MSEL(1); // Set MCLK to MCLK1
    I2S1_TCR3 = I2S_TCR3_TCE; // Enable the first transmit data channel
    I2S1_TCR4 = I2S_TCR4_FRSZ((2 - 1)) // Set 2 words per frame
        | I2S_TCR4_SYWD((32 - 1)) // Set SYNC width to 32;
        | I2S_TCR4_MF // Set MSB first
        | I2S_TCR4_FSD // Set SYNC as an output
        | I2S_TCR4_FSP; // Set SYNC active low
    I2S1_TCR5 = I2S_TCR5_WNW((32 - 1)) // Set the word width to 32
        | I2S_RCR5_W0W((32 - 1)) // Set the word 0 width to 32
        | I2S_RCR5_FBT((32 - 1)); // Set the first bit shifted to 32
}

void Cs4270::setupI2sRx()
{
    I2S1_RMR = 0; // Set the receive mask to 0
    I2S1_RCR1 = I2S_RCR1_RFW(RX_FIFO_WATERMARK); // Set the FIFO watermark
    I2S1_RCR2 = I2S_RCR2_SYNC(0) // Set RX mode to async
        | I2S_RCR2_BCP // Set BCLK active low
        | I2S_RCR2_BCD // Set BCLK as an output
        | I2S_RCR2_DIV(1) // Set bit clock divide to 4
        | I2S_RCR2_MSEL(1); // Set MCLK to MCLK1
    I2S1_RCR3 = I2S_RCR3_RCE; // Enable the first transmit data channel
    I2S1_RCR4 = I2S_RCR4_FRSZ((2 - 1)) // Set 2 words per frame
        | I2S_RCR4_SYWD((32 - 1)) // Set SYNC width to 32;
        | I2S_RCR4_MF // Set MSB first
        | I2S_RCR4_FSD // Set SYNC as an output
        | I2S_RCR4_FSP; // Set SYNC active low
    I2S1_RCR5 = I2S_RCR5_WNW((32-1)) // Set the word width to 32
        | I2S_RCR5_W0W((32-1)) // Set the word 0 width to 32
        | I2S_RCR5_FBT((32-1)); // Set the first bit shifted to 32
}

void Cs4270::setupInterrupt()
{
    leftInputBuffer = &m_leftInputBuffer;
    rightInputBuffer = &m_rightInputBuffer;
    leftOutputBuffer = &m_leftOutputBuffer;
    rightOutputBuffer = &m_rightOutputBuffer;
    attachInterruptVector(IRQ_SAI1, cs4270Interrupt);
}

void Cs4270::enableI2s()
{
    // Offset the output by 1 sample to prevent transmit FIFO errors
    I2S1_TDR0 = 0;
    I2S1_TDR0 = 0;

    // Setup TX/RX pins
    CORE_PIN7_CONFIG  = 3;  // Set pin7 as TX
    CORE_PIN8_CONFIG  = 3;  // Set pin8 as RX
    IOMUXC_SAI1_RX_DATA0_SELECT_INPUT = 2;

    I2S1_TCSR = I2S_TCSR_TE // Enable the transmitter
        | I2S_TCSR_BCE // Enable BCLK
        | I2S_TCSR_FRIE; // Enable transmitter FIFO interrupt

    I2S1_RCSR = I2S_RCSR_RE // Enable the receiver
        | I2S_RCSR_BCE // Enable BCLK
        | I2S_RCSR_FRIE // Enable receiver FIFO interrupt
        | I2S_RCSR_FR; // Reset FIFO
}

float Cs4270::int32ToFloat(int32_t v)
{
    return -static_cast<float>(v) / static_cast<float>(INT32_MIN);
}

int32_t Cs4270::floatToInt32(float v)
{
    if (v < -CLIPPING_VALUE)
    {
        v = INT32_MIN * CLIPPING_VALUE;
    }
    if (v > CLIPPING_VALUE)
    {
        v = INT32_MAX * CLIPPING_VALUE;
    }

    return static_cast<int32_t>(-v * static_cast<float>(INT32_MIN));
}

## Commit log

2020-03-02 Ajout de la shématique pour la partie analogique.
2020-03-02 Ajout de la schématique pour le MCU
2020-03-02 Modification des MOSFET des LED.
2020-03-02 Création d'un projet pour le MCU et finalisation du MCU.
2020-03-02 Ajout du octaver down, ajout du filtre d'anti-aliasing, ajout de l'offset DC et ajout du clipping.
2020-03-02 Enlèvemnt des fichiers de simulation inutile. Ajustement de la fréquence de coupure du filtre d'anti-aliasing.
2020-03-03 Ajout du pcb pour control
2020-03-03 Correction de pad non connecté
2020-03-03 Correciton du PCB (espacements entre les connecteurs et polygon pour pour l'ADC.)
2020-03-03 Ajout des du circuit du psu
2020-03-09 Ajout du connecteur pour la footswitch.
2020-03-09 Ajout du projet et de la schématique de footswitch
2020-03-09 Suppresion des fichier *-bak
2020-03-10 Commencement du PCB pour footswitch
2020-03-10 Ajout du gnd pour le RX/TX du DSP
2020-03-10 Finalisation du PCB de la footswitch. Correction de la position des mounting holes.
2020-03-10 Ajout de documentation dans les schématiques
2020-03-12 Ajout du PCB du PSU
2020-03-12 Ajout du codec et du dsp
2020-03-16 Ajout des pièces du PCB processing au BOM et assignation des footprints du PCB processing
2020-03-17 Ajout d'un lien pour TH
2020-03-22 Add processing PCB
2020-03-22 Remove simulation files
2020-03-26 Ajout des gerber pour control et footswitch.
2020-03-26 Mise à jour du BOM
2020-03-28 Déplacement des PCB dans le dossier electronics.
2020-03-29 Ajout du UI pour: contour, presence, EQ. Ajout du model pour contour et presence
2020-03-29 Ajout de time_plot_widget et du widget pour compressor.
2020-03-29 Ajout des widgets manquants pour les effets et ajout des widget dans la fenêtre principale.
2020-03-30 Correction de la mise à jour du graphique lors du changement de signal
2020-03-30 Refactor des widgets des effets. Complétion du code pour octaver.
2020-03-30 Ajout du model pour l'overdrive. Ajout de la lecture de wav
2020-03-30 Format code
2020-03-30 Correction du nom des axes.
2020-03-30 Ajout du code pour le delay
2020-03-31 Refactor et ajout du reverb
2020-03-31 Ajout du code pour le compresseur
2020-03-31 Ajust attack
2020-03-31 Ajout du code de l'EQ
2020-03-31 cleanup code
2020-04-01 Ajout du code pour calculer les coefficients des filtres pour le contour, la présence et l'EQ.
2020-04-01 Ajout de CompressorDesigner. Correction du nom des tests.
2020-04-02 Ajout du design des filtres butterworth d'ordre 2.
2020-04-02 Changement de l'ordre et des fréquences du filtre pour octaver_up.
2020-04-02 Changement de la fréquence pour presence.
2020-04-02 Ajout de OctaverDesigner. Correction des tests de PresenceDesigner.
2020-04-02 Ajout de DelayDesigner
2020-04-02 Ajout de ReverbDesigner
2020-04-02 Ajout de OverdriveDesigner
2020-04-02 Ajout de l'activation/désactivations des effets.
2020-04-02 Ajout de la classe pour lire les ADC et de la classe pour lire les valeurs de contrôle des effets.
2020-04-02 Ajout de StatusLed
2020-04-02 Ajout de MuteDesigner, commencement du main
2020-04-02 Ajout du contrôleur de la fan.
2020-04-02 Refactor de la structure des dossiers.
2020-04-02 Refactor des effect codes
2020-04-02 Renommage de control à controller.
2020-04-02 Ajout de la classe pour la communication entre le controlleur et la footswitch.
2020-04-03 Ajout de la communication avec la footswitch dans le main de controller. Ajout des éléments manquants dans la communicaiton.
2020-04-03 Utilisation de Ticker dans le main de controller.
2020-04-03 Enlèmevement des fichiers pour Travis.
2020-04-03 Ajout d'un commande manquante pour la communication de la footswitch
2020-04-03 Enlèvement du message ToogleEffect
2020-04-03 Ajout d'un ack dans la communication entre la footswitch et le controller.
2020-04-03 Fix typo.
2020-04-03 Revert of 28c36f07b22f30b18053c4ea3149e90765df471e
2020-04-03 Ajout du code pour la footswitch!
2020-04-04 Ajout du heartbeat, ajout du port série de deboguage, correction des tickers.
2020-04-04 Correction du code pour le Teensy LC.
2020-04-05 Correction du design des filtres.
2020-04-05 Ajout du traitement pour Contour, Presence et Eq.
2020-04-05 Refactor et ajout du compressor et l'octaver pour le MCU
2020-04-05 Refactor et ajout du Delay
2020-04-05 Ajout du reverb dans processing
2020-04-05 Ajout de l'overdrive dans processing.
2020-04-06 Ajout de Mute et de isEnabled dans processing.
2020-04-17 Ajout de la lib manquante
2020-05-06 Corrections
2020-05-07 Changement de la fuse pour le 9v par une efuse
2020-06-06 Correction d'erreurs dans PSU
2020-07-08 Ajout des fichiers gerber pour le projet psu.
2020-07-10 Création des gerber de processing et correction des gerber de psu.
2020-07-10 Ajout de la communication avec le DSP dans controller.
2020-07-10 Correctionn d'un warning.
2020-07-10 Ajout du code pour le dsp.
2020-07-10 Corrections pour la cohérence des libs.
2020-07-10 Correction des messages des static_assert dans Cs4270.
2020-07-10 Correction de copier/coller et ajout de la ligne mettant SAI à on.
2020-07-14 Cleanup
2020-07-30 Ajout de la détection du clipping.
2020-07-31 Correction des interrupts TX.
2020-07-31 Correction du setup des pin du I2S.
2020-08-14 Tab to spaces
2020-08-23 Correction du clipping.
2020-08-23 Correction de la lecture de l'ADC et l'écriture du DAC.
2020-08-23 Correction D-flip-flop
2020-08-28 Correction pour l'intrégration.
2020-09-01 Ajout du transformateur au BOM
2020-09-16 Add README.md
2020-12-22 Fix footswitch
2022-04-03 Switch the down octave processing to the firmware.
2023-08-11 Add the pitch shifter effect to python tool.
2023-08-12 Add pitch shifter code.
2023-08-12 Fix initialization with the new SDK.
2023-08-13 Fix I2S underflow.
